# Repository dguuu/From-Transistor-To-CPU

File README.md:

10/10 I make a 1bit FA in KiCad and make a PCB Layouted with perfboard. The perfboard size is 9x7cm. In other words, it's 26x31 hole. If I got all of the materials I can make it. By the way I chose all 2n7000 based on NMOS logic. Because its easy to get, lower power consumption than BJT logic, not as complex as CMOS logic and also cheap HAHA.
10/12 Today, after modularizing the layout, I redrew the cabling. The cabling is much more elegant now.

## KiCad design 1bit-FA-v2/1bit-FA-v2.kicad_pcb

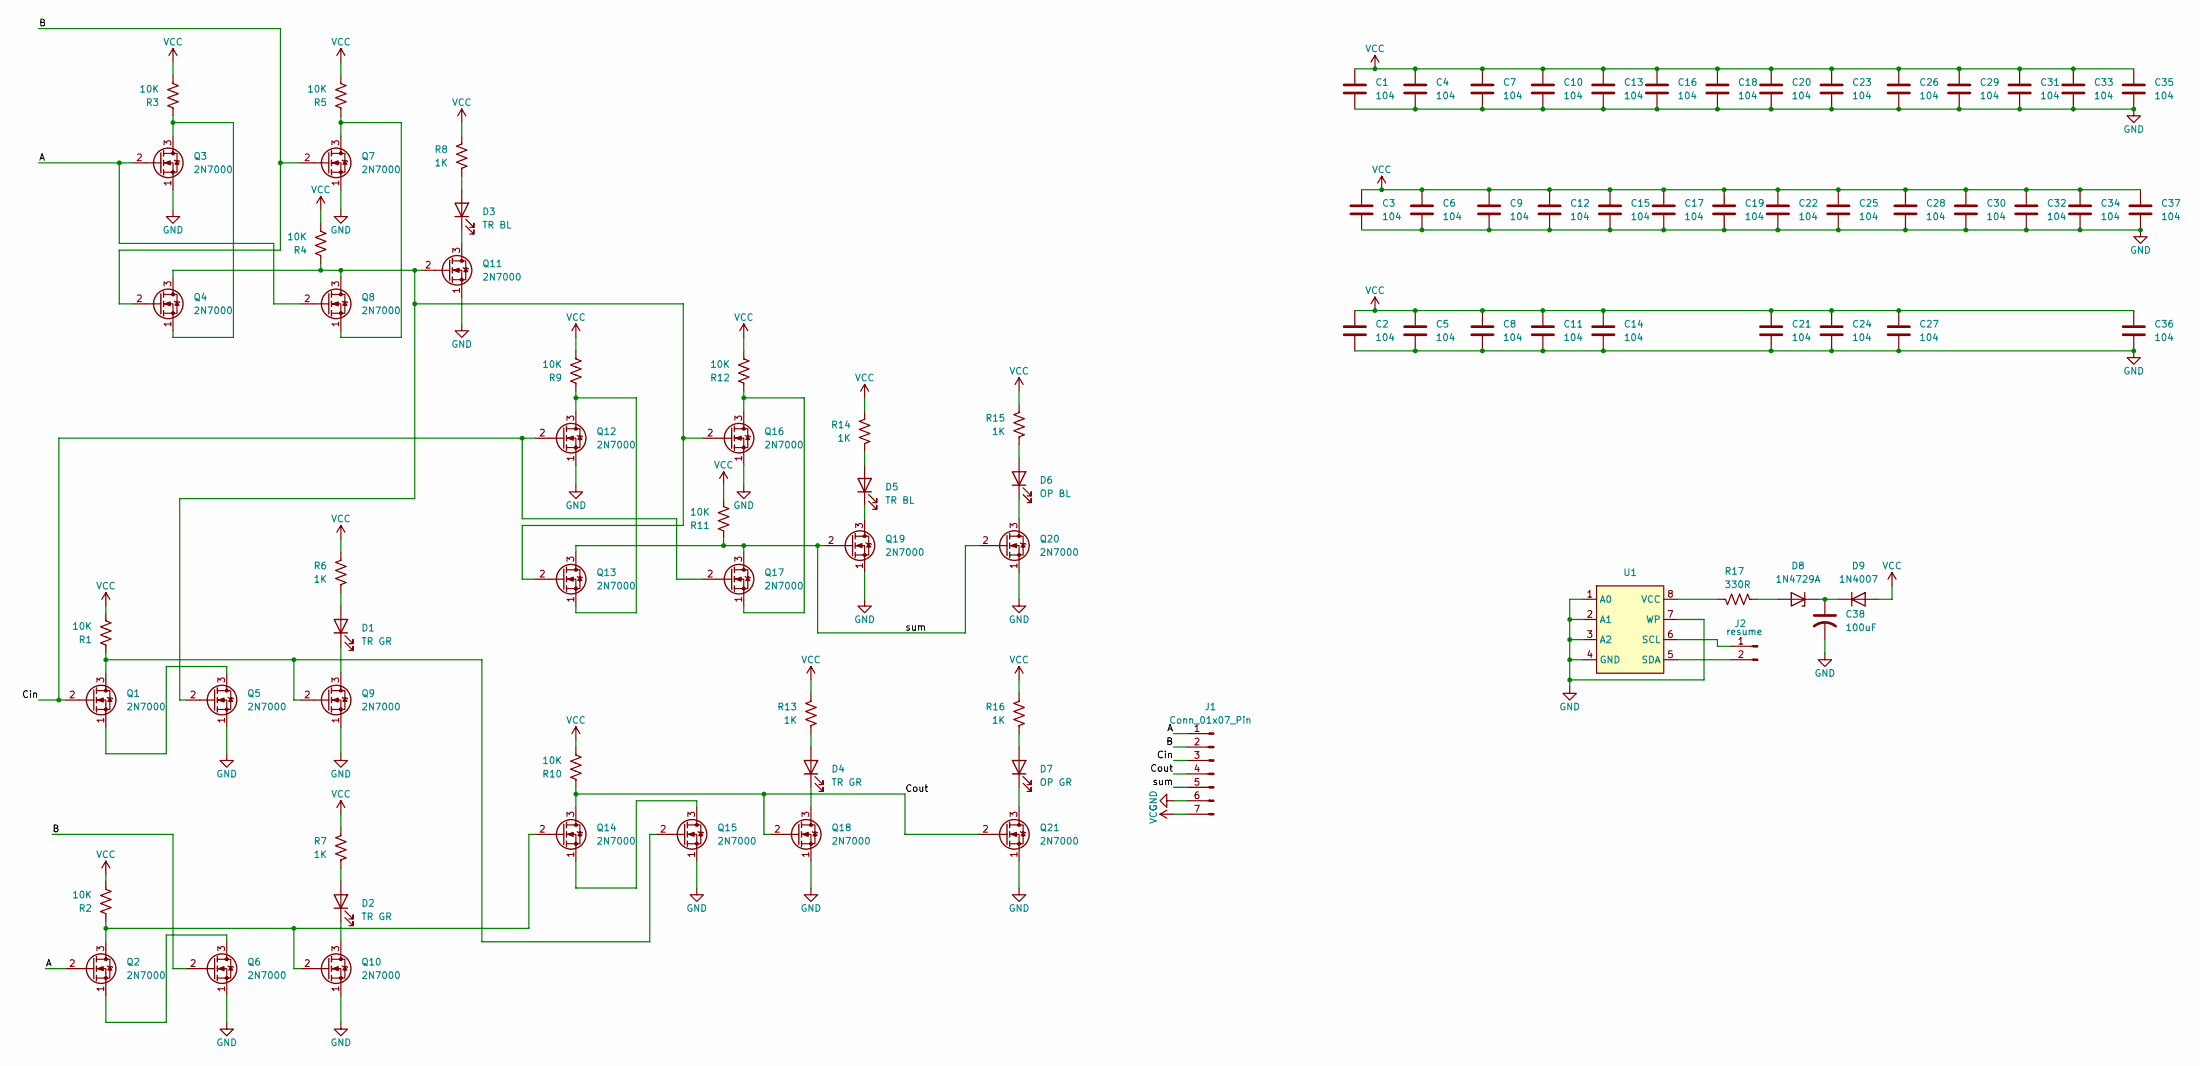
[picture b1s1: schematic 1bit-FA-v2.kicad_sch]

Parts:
C1, C2, C3, C4, C5, C6, C7, C8, C9, C10, C11, C12, C13, C14, C15, C16, C17, C18, C19, C20, C21, C22, C23, C24, C25, C26, C27, C28, C29, C30, C31, C32, C33, C34, C35, C36, C37: 104; C_Disc_D5.0mm_W2.5mm_P2.50mm
C38: 100uF; C_Radial_D10.0mm_H16.0mm_P5.00mm
D1, D2, D4: TR GR; LED_D3.0mm
D3, D5: TR BL; LED_D3.0mm
D6: OP BL; LED_D3.0mm
D7: OP GR; LED_D3.0mm
D8: 1N4729A; D_DO-41_SOD81_P10.16mm_Horizontal
D9: 1N4007; D_DO-41_SOD81_P10.16mm_Horizontal
J1: Conn_01x07_Pin; PinHeader_1x07_P2.54mm_Horizontal
J2: resume; PinHeader_1x02_P2.54mm_Horizontal
Q1, Q2, Q3, Q4, Q5, Q6, Q7, Q8, Q9, Q10, Q11, Q12, Q13, Q14, Q15, Q16, Q17, Q18, Q19, Q20, Q21: 2N7000; TO-92_Inline_Wide_small
R1, R2, R3, R4, R5, R9, R10, R11, R12: 10K; 1_4w-resistor
R6, R7, R8, R13, R14, R15, R16: 1K; 1_4w-resistor
R17: 330R; 1_4w-resistor
U1: DIP-8_W7.62mm

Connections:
/A: J1.1, Q2.2 (G), Q3.2 (G), Q8.2 (G)
/B: J1.2, Q4.2 (G), Q6.2 (G), Q7.2 (G)
/Cin: J1.3, Q1.2 (G), Q12.2 (G), Q17.2 (G)
/Cout: J1.4, Q14.3 (D), Q18.2 (G), Q21.2 (G), R10.1
/sum: J1.5, Q13.3 (D), Q17.3 (D), Q19.2 (G), Q20.2 (G), R11.1
GND: C1.2, C2.2, C3.2, C4.2, C5.2, C6.2, C7.2, C8.2, C9.2, C10.2, C11.2, C12.2, C13.2, C14.2, C15.2, C16.2, C17.2, C18.2, C19.2, C20.2, C21.2, C22.2, C23.2, C24.2, C25.2, C26.2, C27.2, C28.2, C29.2, C30.2, C31.2, C32.2, C33.2, C34.2, C35.2, C36.2, C37.2, C38.2, J1.6, Q3.1 (S), Q5.1 (S), Q6.1 (S), Q7.1 (S), Q9.1 (S), Q10.1 (S), Q11.1 (S), Q12.1 (S), Q15.1 (S), Q16.1 (S), Q18.1 (S), Q19.1 (S), Q20.1 (S), Q21.1 (S), U1.1 (A0), U1.2 (A1), U1.3 (A2), U1.4 (GND), U1.7 (WP)
unnamed: D1.2 (A), R6.1
unnamed: D1.1 (K), Q9.3 (D)
unnamed: D2.2 (A), R7.1
unnamed: D2.1 (K), Q10.3 (D)
unnamed: D3.2 (A), R8.1
unnamed: D3.1 (K), Q11.3 (D)
unnamed: D4.2 (A), R13.1
unnamed: D4.1 (K), Q18.3 (D)
unnamed: D5.2 (A), R14.1
unnamed: D5.1 (K), Q19.3 (D)
unnamed: D6.2 (A), R15.1
unnamed: D6.1 (K), Q20.3 (D)
unnamed: D7.2 (A), R16.1
unnamed: D7.1 (K), Q21.3 (D)
unnamed: D8.2 (A), R17.2
unnamed: C38.1, D8.1 (K), D9.1 (K)
unnamed: J2.1, U1.6 (SCL)
unnamed: J2.2, U1.5 (SDA)
unnamed: Q1.3 (D), Q9.2 (G), Q15.2 (G), R1.1
unnamed: Q1.1 (S), Q5.3 (D)
unnamed: Q2.1 (S), Q6.3 (D)
unnamed: Q3.3 (D), Q4.1 (S), R3.1
unnamed: Q7.3 (D), Q8.1 (S), R5.1
unnamed: Q2.3 (D), Q10.2 (G), Q14.2 (G), R2.1
unnamed: Q4.3 (D), Q5.2 (G), Q8.3 (D), Q11.2 (G), Q13.2 (G), Q16.2 (G), R4.1
unnamed: Q12.3 (D), Q13.1 (S), R9.1
unnamed: Q14.1 (S), Q15.3 (D)
unnamed: Q16.3 (D), Q17.1 (S), R12.1
unnamed: R17.1, U1.8 (VCC)
VCC: C1.1, C2.1, C3.1, C4.1, C5.1, C6.1, C7.1, C8.1, C9.1, C10.1, C11.1, C12.1, C13.1, C14.1, C15.1, C16.1, C17.1, C18.1, C19.1, C20.1, C21.1, C22.1, C23.1, C24.1, C25.1, C26.1, C27.1, C28.1, C29.1, C30.1, C31.1, C32.1, C33.1, C34.1, C35.1, C36.1, C37.1, D9.2 (A), J1.7, R1.2, R2.2, R3.2, R4.2, R5.2, R6.2, R7.2, R8.2, R9.2, R10.2, R11.2, R12.2, R13.2, R14.2, R15.2, R16.2

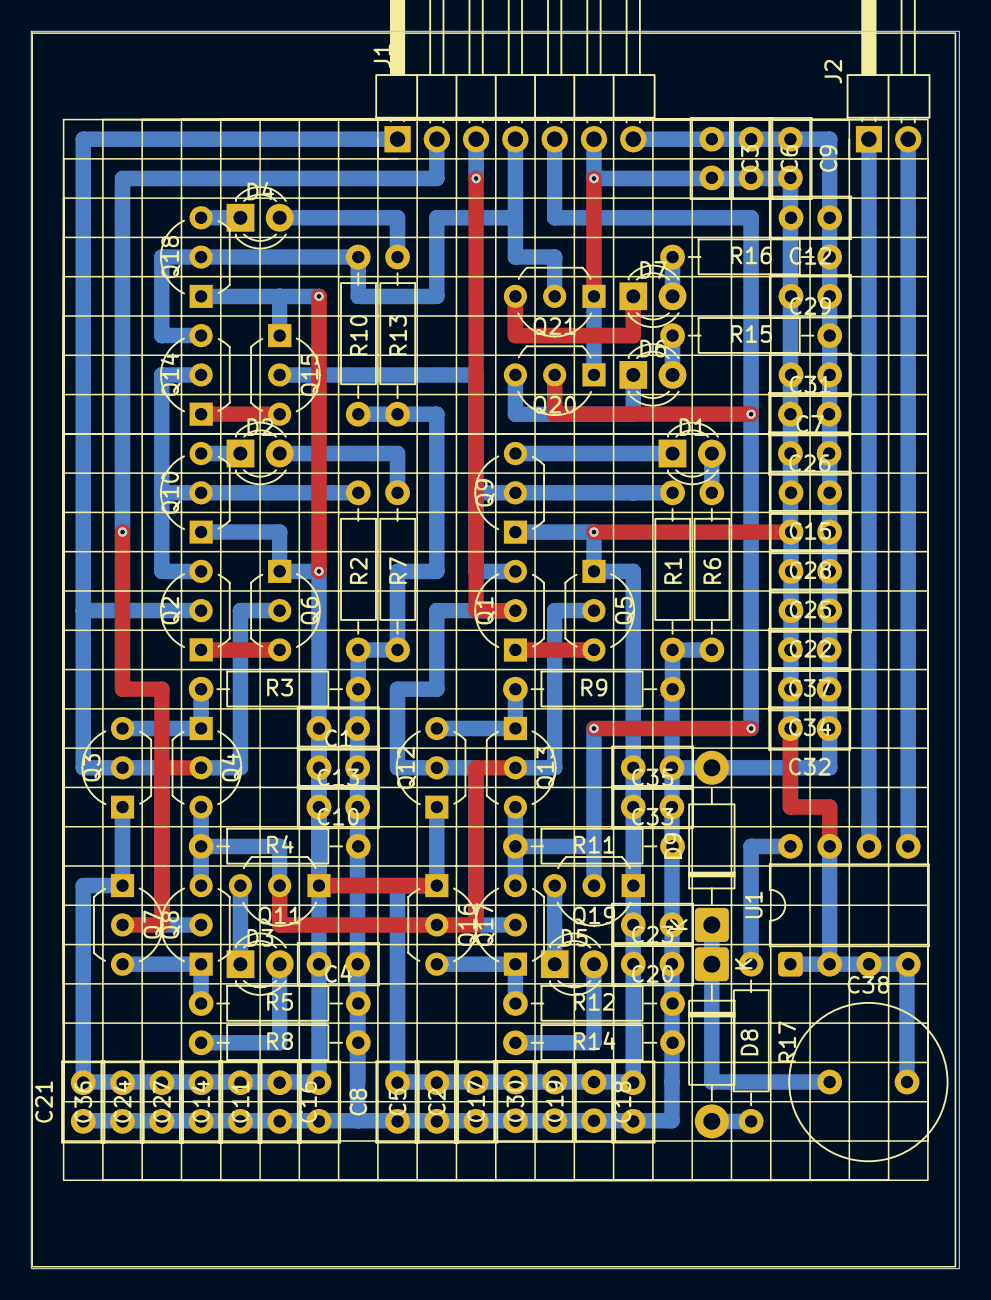
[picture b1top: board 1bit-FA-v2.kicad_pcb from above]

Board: 2 copper layers, 60.0 x 80.0 mm, 88 parts (0 on the bottom side), 36 nets.

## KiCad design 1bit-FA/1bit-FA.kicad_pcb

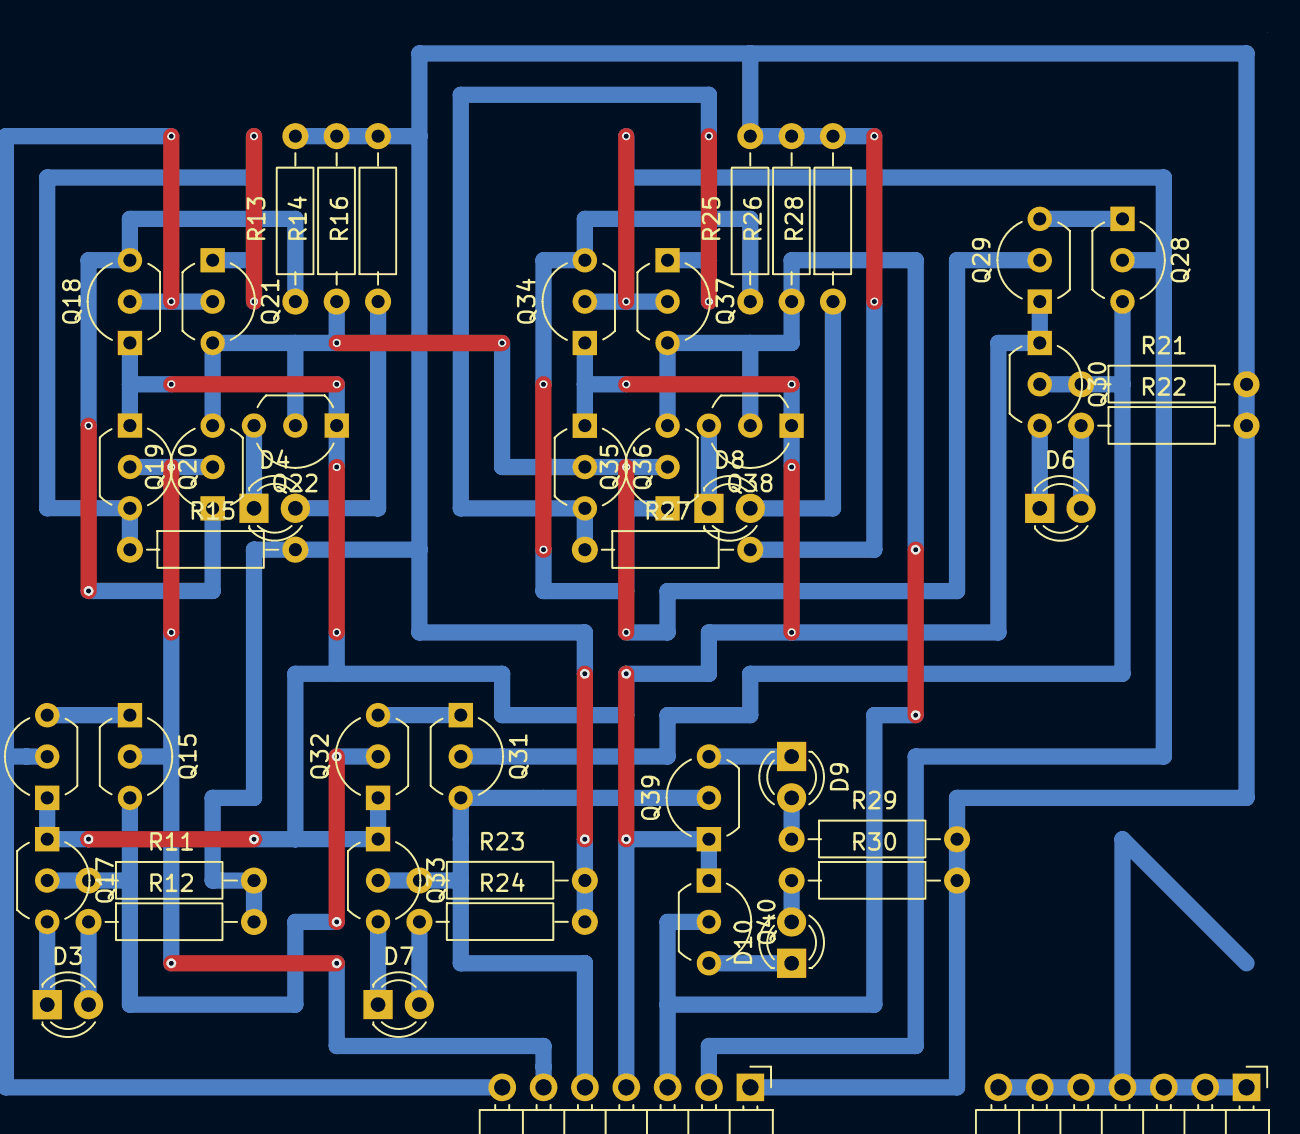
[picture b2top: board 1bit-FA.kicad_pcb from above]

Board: 2 copper layers, 46 parts (0 on the bottom side), 31 nets.

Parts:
D3, D6, D7: TR GR; LED_D3.0mm
D4, D8: TR BL; LED_D3.0mm
D9: OP GR; LED_D3.0mm
D10: OP BL; LED_D3.0mm
J2, J2#2: Conn_01x07_Pin; PinHeader_1x07_P2.54mm_Horizontal
Q15, Q16, Q17, Q18, Q19, Q20, Q21, Q22, Q28, Q29, Q30, Q31, Q32, Q33, Q34, Q35, Q36, Q37, Q38, Q39, Q40: 2N7000; TO-92_Inline_Wide_small
R11, R13, R14, R15, R21, R23, R25, R26, R27: 10K; 1_4w-resistor
R12, R16, R22, R24, R28, R29, R30: 1K; 1_4w-resistor

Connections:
/A: J2#2.6, Q15.2 (G), Q19.2 (G), Q20.2 (G)
/B: J2#2.7, Q16.2 (G), Q18.2 (G), Q21.2 (G)
/Cin: J2#2.2, Q28.2 (G), Q34.2 (G), Q37.2 (G)
/Cout: J2#2.5, Q31.3 (D), Q33.2 (G), Q39.2 (G), R23.1
/sum: J2#2.3, Q35.3 (D), Q37.3 (D), Q38.2 (G), Q40.2 (G), R26.1
GND: J2#2.4, Q16.1 (S), Q17.1 (S), Q18.1 (S), Q20.1 (S), Q22.1 (S), Q29.1 (S), Q30.1 (S), Q32.1 (S), Q33.1 (S), Q34.1 (S), Q36.1 (S), Q38.1 (S), Q39.1 (S), Q40.1 (S)
unnamed: D3.2 (A), R12.1
unnamed: D3.1 (K), Q17.3 (D)
unnamed: D4.2 (A), R16.1
unnamed: D4.1 (K), Q22.3 (D)
unnamed: D6.2 (A), R22.1
unnamed: D6.1 (K), Q30.3 (D)
unnamed: D7.2 (A), R24.1
unnamed: D7.1 (K), Q33.3 (D)
unnamed: D8.2 (A), R28.1
unnamed: D8.1 (K), Q38.3 (D)
unnamed: D9.2 (A), R29.1
unnamed: D9.1 (K), Q39.3 (D)
unnamed: D10.2 (A), R30.1
unnamed: D10.1 (K), Q40.3 (D)
unnamed: Q15.3 (D), Q17.2 (G), Q32.2 (G), R11.1
unnamed: Q15.1 (S), Q16.3 (D)
unnamed: Q18.3 (D), Q19.1 (S), R13.1
unnamed: Q19.3 (D), Q21.3 (D), Q22.2 (G), Q29.2 (G), Q35.2 (G), Q36.2 (G), R14.1
unnamed: Q20.3 (D), Q21.1 (S), R15.1
unnamed: Q28.3 (D), Q30.2 (G), Q31.2 (G), R21.1
unnamed: Q28.1 (S), Q29.3 (D)
unnamed: Q31.1 (S), Q32.3 (D)
unnamed: Q34.3 (D), Q35.1 (S), R25.1
unnamed: Q36.3 (D), Q37.1 (S), R27.1
VCC: J2#2.1, R11.2, R12.2, R13.2, R14.2, R15.2, R16.2, R21.2, R22.2, R23.2, R24.2, R25.2, R26.2, R27.2, R28.2, R29.2, R30.2
